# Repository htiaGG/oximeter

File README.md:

# DIY Oximeter

## Project Overview
This repository contains the code and documentation for a DIY oximeter project, developed as part of a university coursework. The oximeter measures the oxygen saturation level in the blood and heart rate using a combination of hardware sensors and software algorithms.
Two PCBs are used, one housing the dual LED emitter that emits red and infrared light. The other PCB houses the photodiode that continuously measures the modulated light that has passed through the blood vessels of the finger. A Pico MCU ADC picks up this signal and interprets it as the heart rate and SpO2.

## Table of Contents
- [Features](#features)
- [Hardware Used](#hardware-requirements)
- [Software Requirements](#software-requirements)

## Features
- Measures blood oxygen saturation (SpO2)
- Measures heart rate
- Sends readings to the connected PC to display data

## Hardware Used
- vemd8080 Silicon PIN Photodiode
- vsmd66694 Dual Color Emitting Diodes, 660 nm and 940 nm
- OPA2380 Precision, High-Speed Transimpedance Amplifier
- MMBT2222A Switching transistor
- Raspberry Pi Pico W Microcontroller

## Software Requirements
- Python3
- pip install -r requirements.txt

## Dual LED Emitter Circuit Schematic

## Photodiode Circuit Schematic

## Showcase

p.s: the custom 3d printed housing was terrible so i used a clothespin :D

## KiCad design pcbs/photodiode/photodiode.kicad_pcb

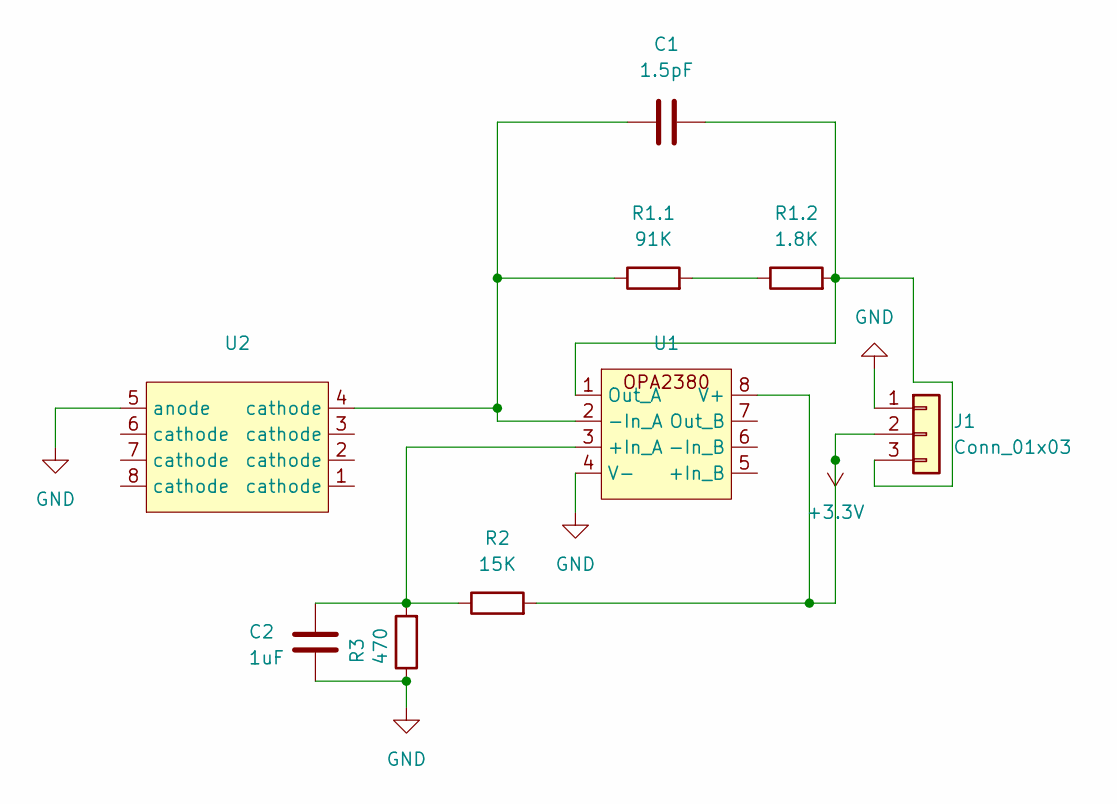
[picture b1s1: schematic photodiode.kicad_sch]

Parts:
C1: 1.5pF; C_0805_2012Metric_Pad1.18x1.45mm_HandSolder
C2: 1uF; C_0805_2012Metric_Pad1.18x1.45mm_HandSolder
J1: Conn_01x03; PinSocket_1x03_P2.54mm_Horizontal
R1.1: 91K; R_0805_2012Metric_Pad1.20x1.40mm_HandSolder
R1.2: 1.8K; R_0805_2012Metric_Pad1.20x1.40mm_HandSolder
R2: 15K; R_0805_2012Metric_Pad1.20x1.40mm_HandSolder
R3: 470; R_0805_2012Metric_Pad1.20x1.40mm_HandSolder
U1: opa2380-v2
U2: vemd8080

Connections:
+3.3V: J1.2, R2.2, U1.8 (V+)
GND: C2.1, J1.1, R3.1, U1.4 (V-), U2.5 (anode)
unnamed: C1.2, J1.3, R1.2.2, U1.1 (Out_A)
unnamed: R1.1.2, R1.2.1
unnamed: C2.2, R2.1, R3.2, U1.3 (+In_A)
unnamed: C1.1, R1.1.1, U1.2 (-In_A), U2.4 (cathode)

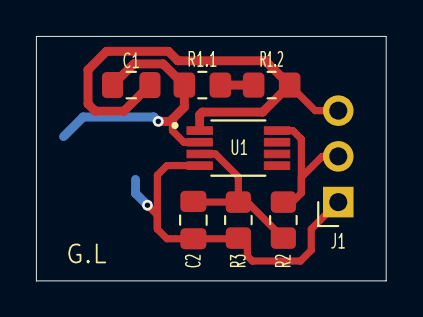
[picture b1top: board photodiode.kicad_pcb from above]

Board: 2 copper layers, 19.4 x 13.6 mm, 9 parts (1 on the bottom side), 6 nets.

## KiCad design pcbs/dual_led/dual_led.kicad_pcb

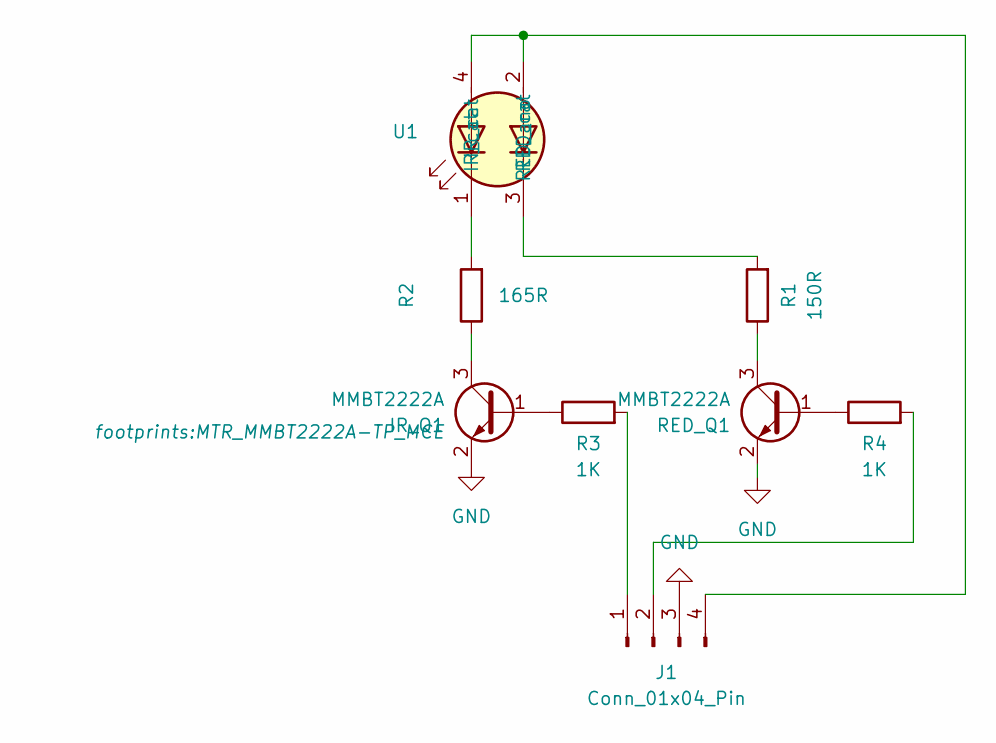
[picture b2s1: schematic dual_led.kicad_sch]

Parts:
IR_Q1: MMBT2222A; MTR_MMBT2222A-TP_MCE
J1: Conn_01x04_Pin; PinSocket_1x04_P2.54mm_Horizontal
R1: 150R; R_0805_2012Metric_Pad1.20x1.40mm_HandSolder
R2: 165R; R_0805_2012Metric_Pad1.20x1.40mm_HandSolder
R3, R4: 1K; R_0805_2012Metric_Pad1.20x1.40mm_HandSolder
RED_Q1: MMBT2222A; MTR_MMBT2222A-TP_MCE
U1: vsmd

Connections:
GND: IR_Q1.2 (E), J1.3, RED_Q1.2 (E)
unnamed: IR_Q1.1 (B), R3.1
unnamed: IR_Q1.3 (C), R2.1
unnamed: J1.1, R3.2
unnamed: J1.2, R4.2
unnamed: J1.4, U1.2 (RED_ano), U1.4 (IR_cat)
unnamed: R2.2, U1.1 (IR_cat)
unnamed: R4.1, RED_Q1.1 (B)
unnamed: R1.1, RED_Q1.3 (C)
unnamed: R1.2, U1.3 (RED_cat)

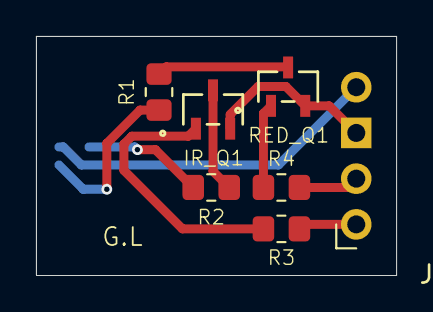
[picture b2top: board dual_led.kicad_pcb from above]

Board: 2 copper layers, 20.0 x 13.3 mm, 8 parts (1 on the bottom side), 10 nets.

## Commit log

2024-09-27 Add README.md
2024-09-27 Add pcb files
2024-09-29 Uploaded script files
2024-09-30 Update resources and README
